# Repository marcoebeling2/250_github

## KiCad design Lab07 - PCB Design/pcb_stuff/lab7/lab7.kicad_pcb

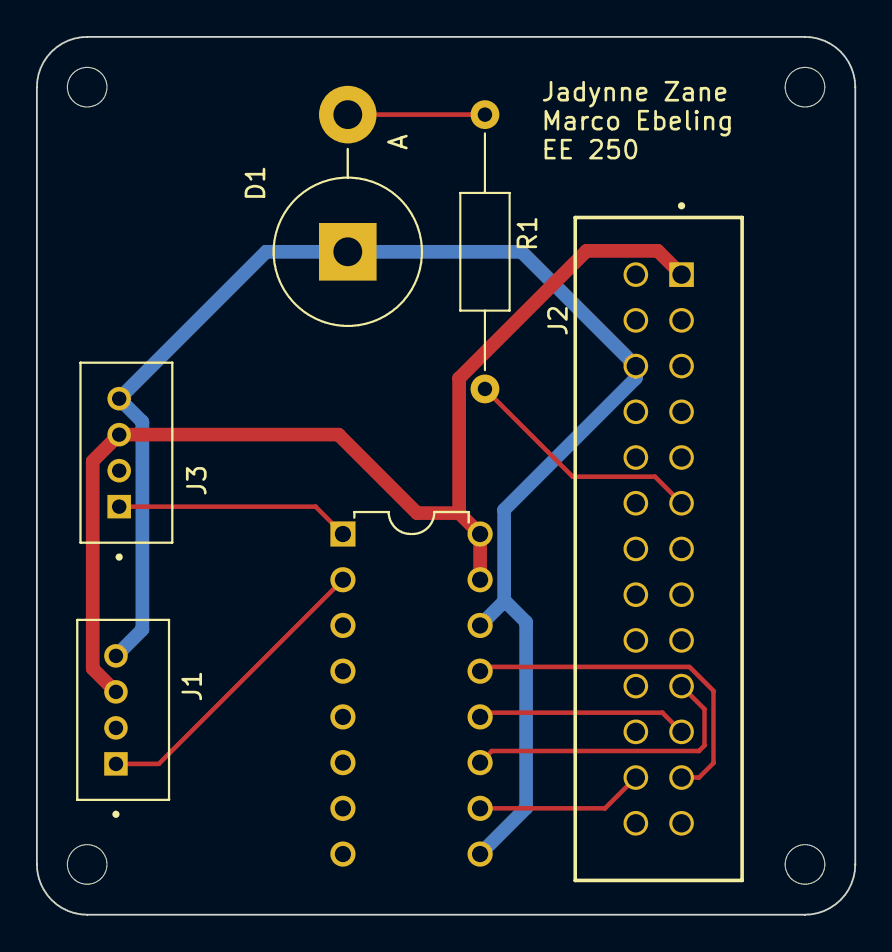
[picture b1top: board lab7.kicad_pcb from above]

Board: 2 copper layers, 45.5 x 48.8 mm, 6 parts (0 on the bottom side), 10 nets.

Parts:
D1: LED; D_5KPW_P7.62mm_Vertical_AnodeUp
J1, J3: 110990030; SEEED_110990030
J2: TSS-113-01-S-D; SAMTEC_TSS-113-01-S-D
R1: 100k; R_Axial_DIN0207_L6.3mm_D2.5mm_P15.24mm_Horizontal
U1: MCP3008-I/P-DIP16; DIP16-2.54-19.2X7.62MM

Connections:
GND: D1.1 (K), J1.4, J2.06, J3.4, U1.9 (DGND), U1.14 (AGND)
unnamed: D1.2 (A), R1.1
unnamed: J2.11, R1.2
unnamed: J3.1, U1.1 (CH0)
unnamed: J1.1, U1.2 (CH1)
unnamed: J2.23, U1.13 (CLK)
unnamed: J2.19, U1.11 (DIN)
unnamed: J2.21, U1.12 (DOUT)
unnamed: J2.24, U1.10 (SHDN/~CS)
VDD: J1.3, J2.01, J3.3, U1.15 (VREF), U1.16 (VDD)

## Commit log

2025-02-03 1st commit
2025-02-03 py code
2025-02-03 questions
2025-02-04 lab03
2025-02-05 gugy
2025-02-05 delete
2025-02-12 lab4
2025-03-05 guy6
2025-04-01 beast
